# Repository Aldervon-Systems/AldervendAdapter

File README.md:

# AldervendAdapter

This repo contains all the firmware and hardware for the AldervendAdapter.

If you're looking for the latest docs/builds, see our [Releases Page](https://github.com/Aldervon-Systems/AldervendAdapter/releases).

# Getting Started

First, clone this repo (and optionally checkout a branch)

```shell
git clone https://github.com/Aldervon-Systems/AldervendAdapter.git
cd AldervendAdapter
```

# Init Submodules

Some libraries and resources are included as submodules, run the following
command to initialize them before opening the main sch

(If you get a missing library error, make sure to do this)

```shell
git submodule update --init --recursive
```

## Project Layout

If you want to use this project template for yourself, you can find it [here!](https://github.com/KenwoodFox/Project-Template)

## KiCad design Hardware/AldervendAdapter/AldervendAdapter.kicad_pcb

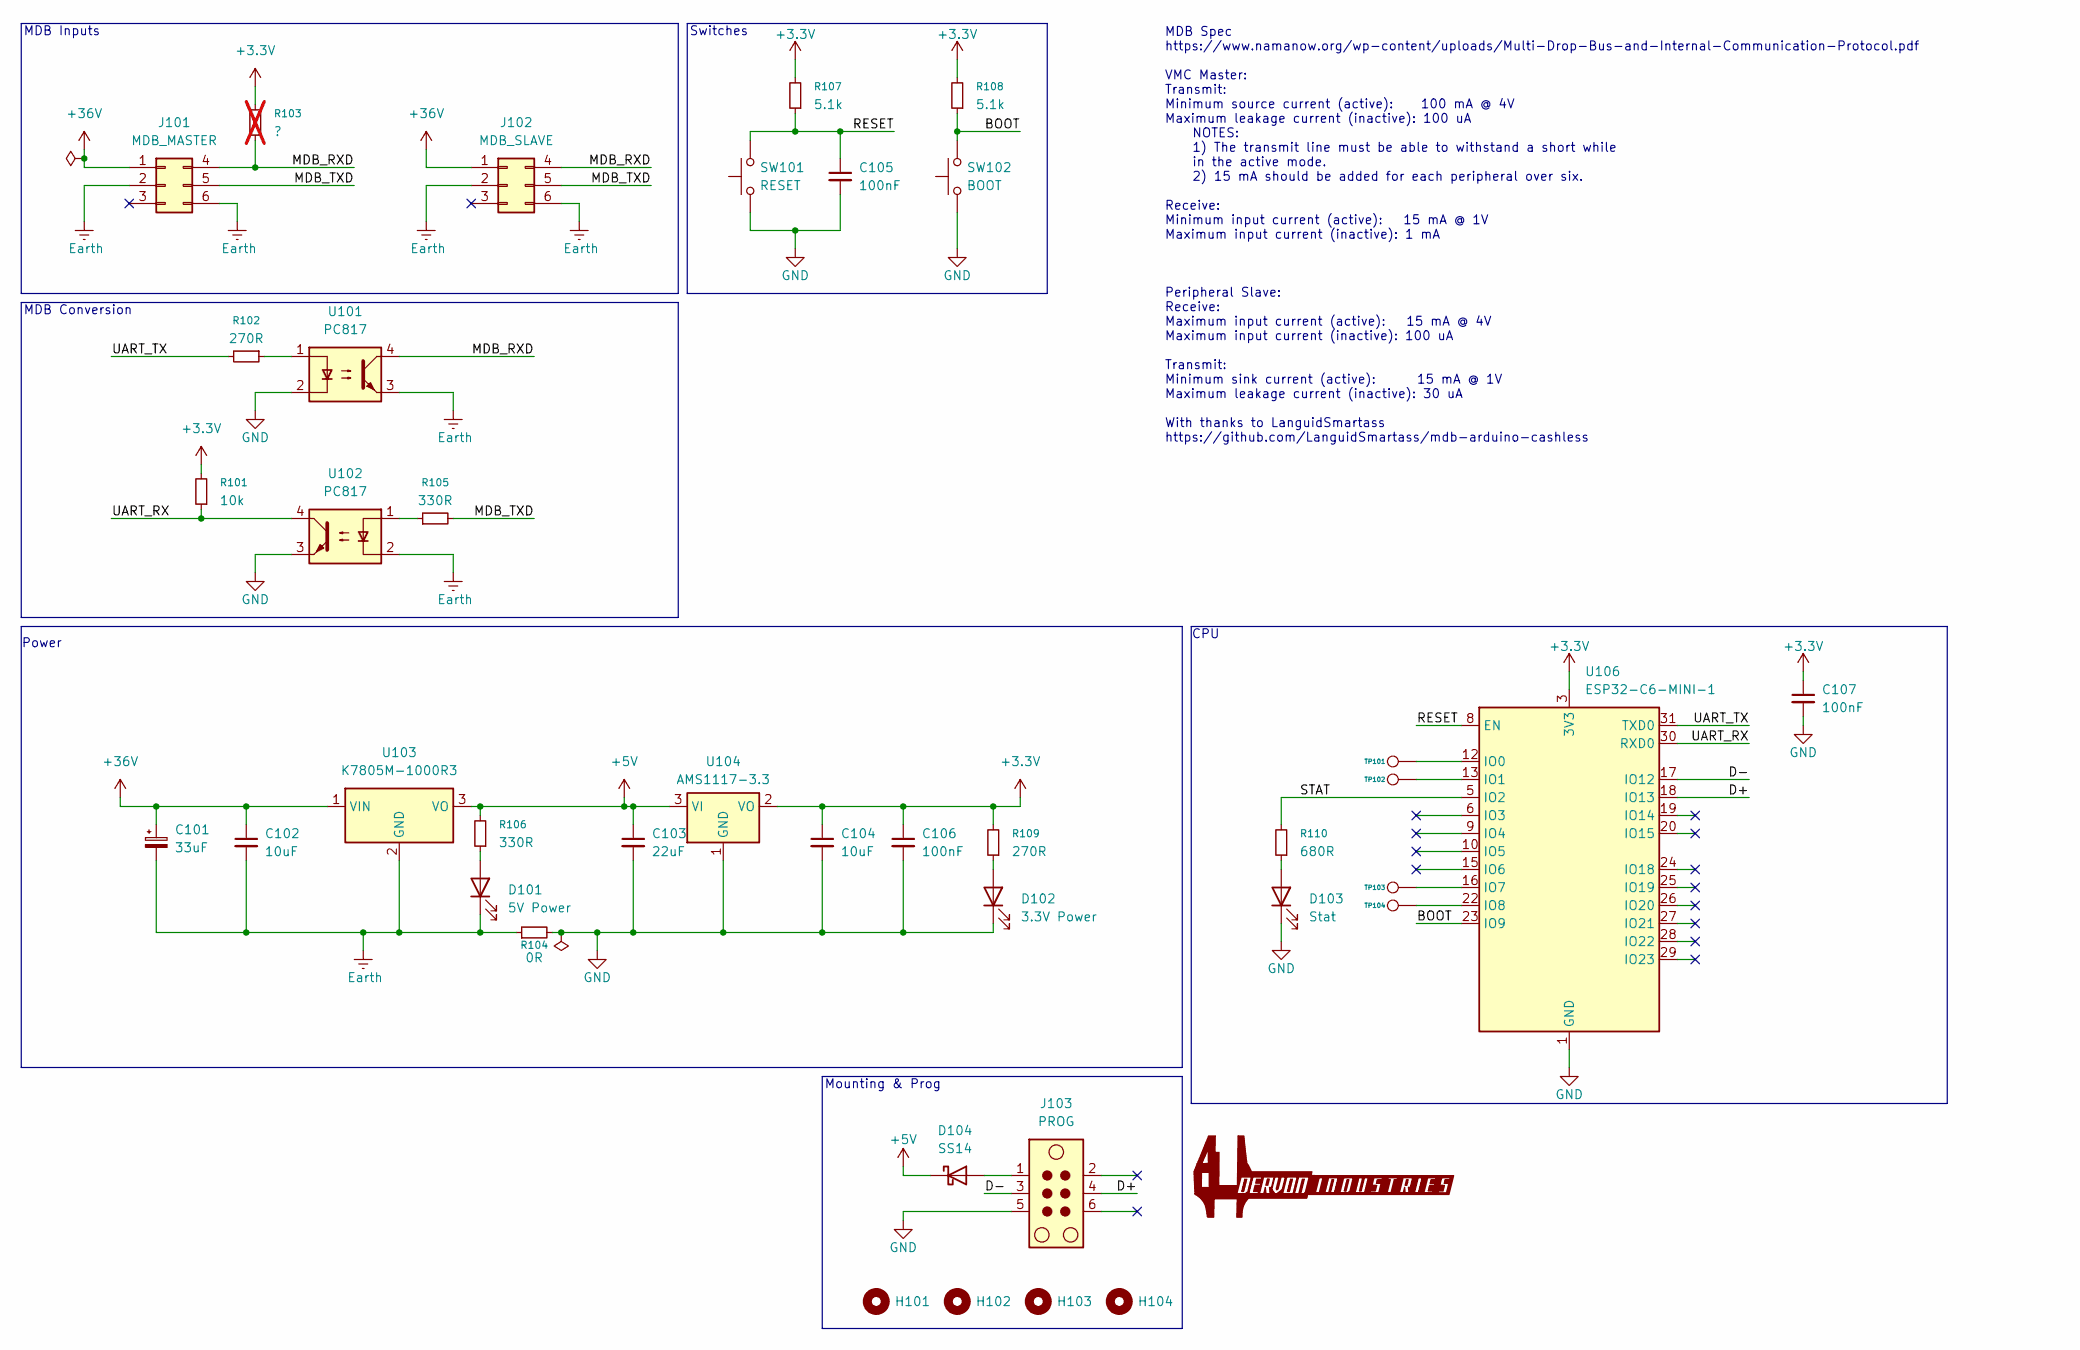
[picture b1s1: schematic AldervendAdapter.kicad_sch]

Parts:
C101: 33uF; CP_Elec_6.3x5.4; LCSC# C27784
C102, C104: 10uF; C_0805_2012Metric; LCSC# C440198
C103: 22uF; C_Elec_4x5.4; LCSC# C3356
C105, C106, C107: 100nF; C_0805_2012Metric; LCSC# C49678
D101: 5V Power; LED_0805_2012Metric; LCSC# C19171391
D102: 3.3V Power; LED_0805_2012Metric; LCSC# C19171391
D103: Stat; LED_0805_2012Metric; LCSC# C19171391
D104: SS14; D_SMA; LCSC# C83852
H101, H102, H103, H104: MountingHole; MountingHole_4.3mm_M4
J101: MDB_MASTER; Molex_Mini-Fit_Jr_5569-06A2_2x03_P4.20mm_Horizontal
J102: MDB_SLAVE; Molex_Mini-Fit_Jr_5569-06A2_2x03_P4.20mm_Horizontal
J103: PROG; Tag-Connect_TC2030-IDC-FP_2x03_P1.27mm_Vertical
R101: 10k; R_0805_2012Metric; LCSC# C84376
R102, R109: 270R; R_0805_2012Metric; LCSC# C17590
R103: ?; R_0805_2012Metric; not fitted
R104: 0R; R_0805_2012Metric; LCSC# C17477
R105, R106: 330R; R_0805_2012Metric; LCSC# C17630
R107, R108: 5.1k; R_0805_2012Metric; LCSC# C27834
R110: 680R; R_0805_2012Metric; LCSC# C114549
SW101: RESET; SW_Push_1P1T_NO_CK_KMR2; LCSC# C221676
SW102: BOOT; SW_Push_1P1T_NO_CK_KMR2; LCSC# C221676
TP101, TP102, TP103, TP104: TestPoint; TestPoint_Pad_2.0x2.0mm
U101, U102: PC817; SMDIP-4_W9.53mm; LCSC# C66405
U103: K7805M-1000R3; LCSC# C5369649
U104: AMS1117-3.3; SOT-223-3_TabPin2; LCSC# C6186
U105: (no value)
U106: ESP32-C6-MINI-1; LCSC# C5736265

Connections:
+3.3V: C104.1, C106.1, C107.1, R101.2, R103.1, R107.2, R108.2, R109.2, U104.2 (VO), U106.3 (3V3)
+5V: C103.1, D104.1 (K), R106.2, U103.3 (VO), U104.3 (VI)
+36V: C101.1, C102.1, J101.1, J102.1, U103.1 (VIN)
/BOOT: R108.1, SW102.2, U106.23 (IO9)
/D+: J103.4, U106.18 (IO13)
/D-: J103.3, U106.17 (IO12)
/MDB_RXD: J101.4, J102.4, R103.2, U101.4
/MDB_TXD: J101.5, J102.5, R105.2
/RESET: C105.1, R107.1, SW101.2, U106.8 (EN)
/STAT: R110.2, U106.5 (IO2)
/UART_RX: R101.1, U102.4, U106.30 (RXD0)
/UART_TX: R102.2, U106.31 (TXD0)
Earth: C101.2, C102.2, D101.1 (K), J101.2, J101.6, J102.2, J102.6, R104.1, U101.3, U102.2, U103.2 (GND)
GND: C103.2, C104.2, C105.2, C106.2, C107.2, D102.1 (K), D103.1 (K), J103.5, R104.2, SW101.1, SW102.1, U101.2, U102.3, U104.1 (GND), U106.1 (GND), U106.2 (GND), U106.11 (GND), U106.14 (GND), U106.36 (GND), U106.37 (GND), U106.38 (GND), U106.39 (GND), U106.40 (GND), U106.41 (GND), U106.42 (GND), U106.43 (GND), U106.44 (GND), U106.45 (GND), U106.46 (GND), U106.47 (GND), U106.48 (GND), U106.49 (GND), U106.50 (GND), U106.51 (GND), U106.52 (GND), U106.53 (GND)
unnamed: D101.2 (A), R106.1
unnamed: D102.2 (A), R109.1
unnamed: D103.2 (A), R110.1
unnamed: D104.2 (A), J103.1
unnamed: R102.1, U101.1
unnamed: R105.1, U102.1
unnamed: TP101.1, U106.12 (IO0)
unnamed: TP102.1, U106.13 (IO1)
unnamed: TP103.1, U106.16 (IO7)
unnamed: TP104.1, U106.22 (IO8)

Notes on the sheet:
CPU
Mounting & Prog
Switches
MDB Spec https://www.namanow.org/wp-content/uploads/Multi-Drop-Bus-and-Internal-Communication-Protocol.pdf VMC Master: Transmit: Minimum source current (active): 100 mA @ 4V Maximum leakage current (inactive): 100 uA NOTES: 1) The transmit line must be able to withstand a short while in the active 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
MDB Conversion
Power
MDB Inputs

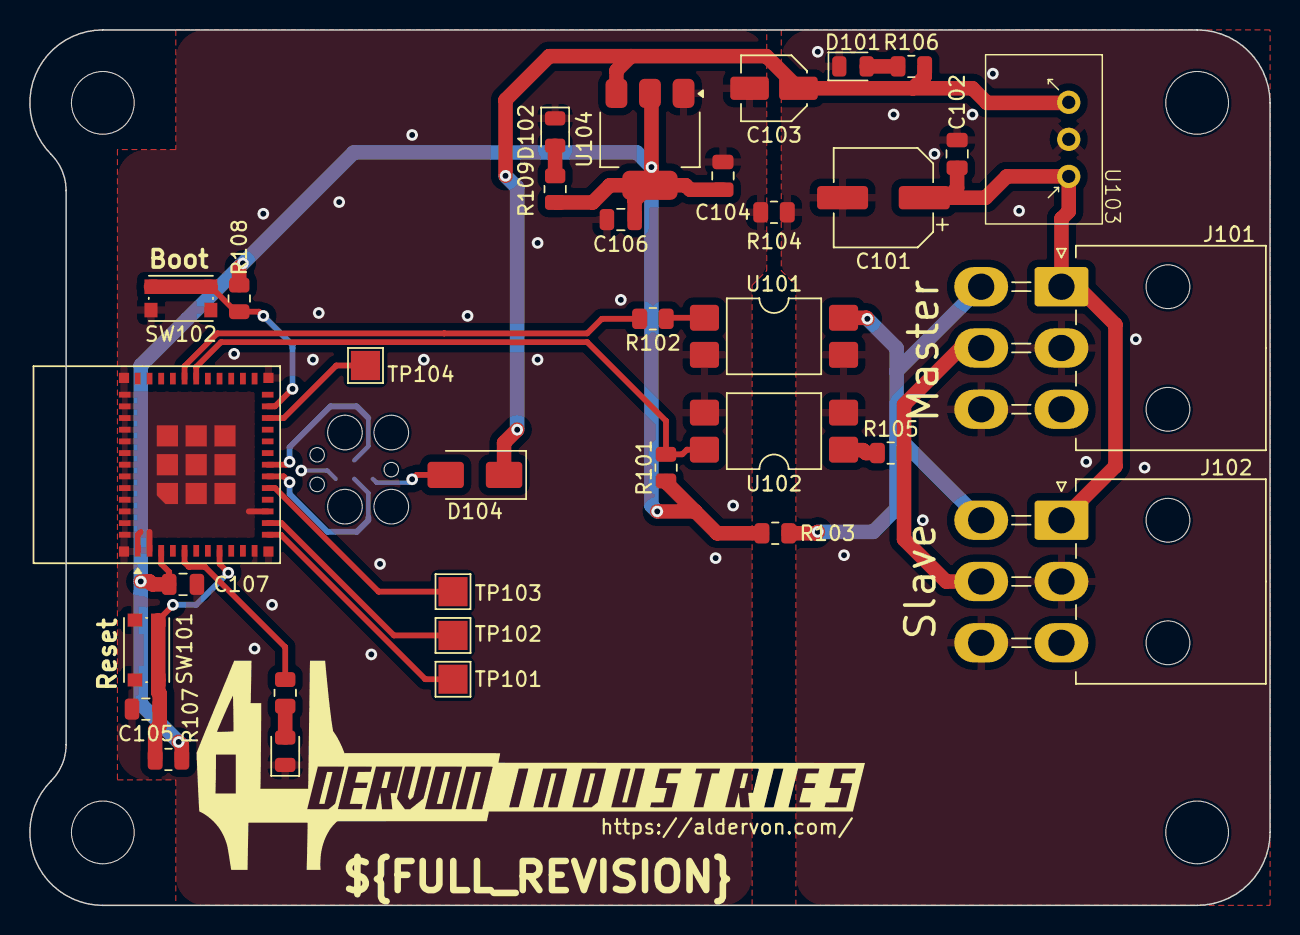
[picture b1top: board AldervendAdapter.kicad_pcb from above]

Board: 2 copper layers, 85.0 x 60.0 mm, 39 parts (1 on the bottom side), 24 nets.

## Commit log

2026-01-25 Import from https://github.com/KenwoodFox/Project-Template
2026-01-26 Bump MVD
2026-01-26 Add aldervon logo
2026-01-27 Add 3d
2026-01-27 skip DRC
2026-01-27 Enforce export 3d
2026-01-28 Add some sch work
2026-02-09 Enough free work for today
2026-02-12 Make aldervon logo
2026-02-21 Settle in on a vrm and other optos
2026-02-21 bump ci
2026-02-21 Fix json
2026-02-21 Bump
2026-02-21 Swap ls for find
2026-02-21 Finish schematic
2026-02-21 Add all but finishing touches
2026-02-21 Find some replacement parts for standard assembly
2026-02-22 last
2026-02-22 Add final
2026-02-22 Assign LCSC for THT parts
2026-02-22 Last style
2026-02-22 Create inital 3d models
2026-02-23 Add stencil for PCB tht assembly
2026-02-23 CLean sketch, finish fab (3d print)
2026-02-23 Fix manufacturing width for iso
2026-03-01 Inital OTA template
2026-03-01 post build fw run script
2026-03-01 Fix workflow
2026-03-02 clean all
2026-03-02 Add more for portal
2026-03-02 Fix sizing
2026-03-02 Finally fix partitions
2026-03-02 Finally device registraion
2026-03-02 Prep for bulk
2026-03-02 Make an MDB simulation task and outline finals
2026-03-02 Add timeouts
2026-03-02 Add device key generation for future HMAC
2026-03-02 Add back basic OTA
2026-03-02 Bake OTA
2026-03-02 Remove unsued
2026-03-03 Two OTA slots
2026-03-03 vbin
2026-03-03 I'd say updates work
2026-03-03 Make most of a cat herder
2026-03-03 Basic docker
2026-03-03 Add some notes
2026-03-03 Fix index and run (for allow api
2026-03-03 Fix an issue with http stack overflow for on-device config
2026-03-03 Add boot button pin
2026-03-03 Ignore cache
2026-03-03 use boot button for wifi reset
2026-03-06 Add inital case
2026-03-06 include pins
2026-03-06 Fix component direction
2026-03-06 Finalize top case
2026-03-06 Increase depth on bottom of case
2026-03-06 Remove prototype branding
